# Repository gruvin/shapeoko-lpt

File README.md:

# Shapeoko UCCNC Upgrade

### Replacing [Shapeoko Pro XL](https://shop.carbide3d.com/collections/machines/products/shapeoko-pro-cnc-router?variant=33007028797501) basic stepper drivers and ditching GRBL in favour of advanced [UCCNC](https://cncdrive.com/UCCNC.html) Controller, using [UC100](https://cncdrive.com/UC100.html) USB interface to plug into this board.

## Why?

Mostly because I really like being able to pause, rewind, start, stop and see toolpaths in realtime. Call me old fashion. 

As a bonus, we get waaaaaay smoother, faster and generally more reliable stepper motors, using "proper" drivers.

## Features

Firstly, I didn't want to cut any wires ...

- Uses original Carbide3D Shapeoko power brick 24VDC @ 5A. (MOSFET switch and onboard 5V supply should handle double that V/A no problem.)
- Uses all original Shapeoko connectors for Power Switch (with blue LED), End Stops, BitSetter & BitZero. (An adapter board for the stepper motors is coming. The latter will be one each for the motor outputs on the stepper drivers.)

... etcetera ...
- Connects to your choice of "decent" stepper drivers

- Provides 24VDC/5A Charge Pump Switched power for drivers. Each of X/Y/Z ports has +5V/STEP/DIR/EN outputs (active low and Y1/Y2 are wired in parrallel or series. Your chpoice.)

- Built-in safety "charge pump" prevents 24VDC coming live until UCCNC is up and ready on the PC (can be bypassed with jumper.)

- VFD Spindle control with 0-10V speed control

- External 3 relay connector (4 if no charge pump). Relay 1 of 4 operates from EN (stepper enable). Relay 2 and 3 are connected to LPT P8 and P9 (Flood/Mist/Vacuum/Air.)

- Onboard 5VDC 1A supply.

- Input for **!! EMMERGENCY STOP !!** (normally closed switch.) Currently, the signal just goes to LPT P1, for your controller software (USCNC/Mach3) to deal with. Can use for that or Feed Hold if preferred.

## Status
### 2022-06-02 

First batch of assembled prototype PCBs were a bust due to both errors and having been obsoleted by lots of design changes since ordering them.

Trying to get a full week without making any chages before ordering a set of V2.0.

### KiCAD sneak peek, very much a work in progress ...

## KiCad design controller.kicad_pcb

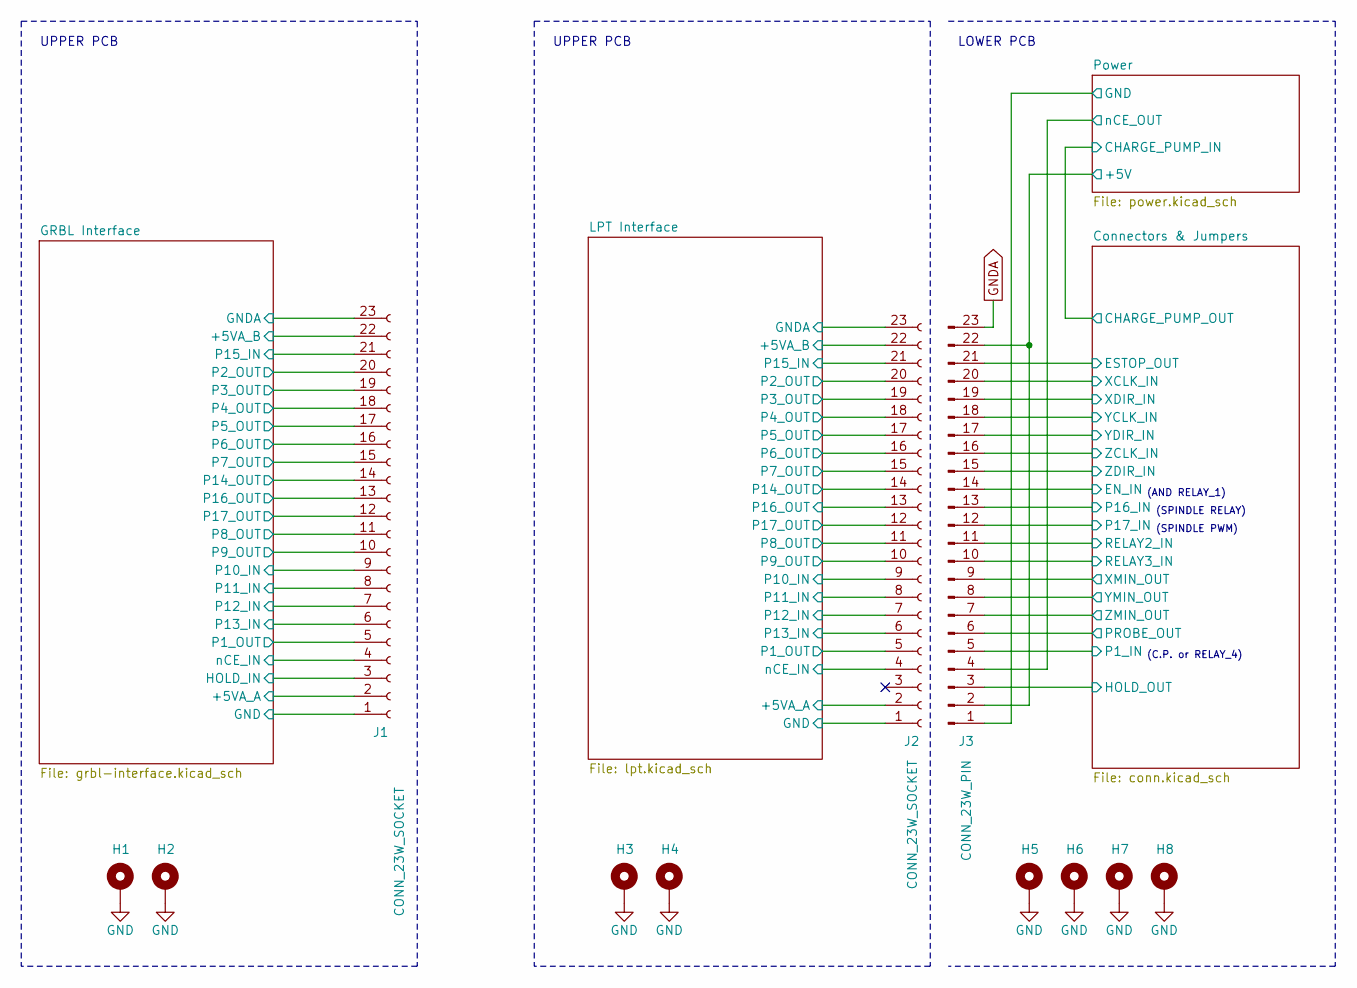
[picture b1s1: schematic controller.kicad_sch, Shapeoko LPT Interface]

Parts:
H1, H2, H3, H4, H6, H8: MountingHole_Pad; MountingHole_3.2mm_M3_ISO14580_Pad; JLCPART DNI
H5, H7: MountingHole_Pad; MountingHole_3.2mm_M3_ISO14580_Pad; JLCMFR# DNI
J1, J2: CONN_23W_SOCKET; PinSocket_1x23_P2.54mm_Vertical; LCSC C41376162
J3: CONN_23W_PIN; PinHeader_1x23_P2.54mm_Vertical

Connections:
+5V: J3.2, J3.22; also elsewhere on the board
+5VA: J1.2, J1.22, J2.2, J2.22; also elsewhere on the board
/Connectors & Jumpers/EN_IN: J3.14; also elsewhere on the board
/Connectors & Jumpers/ESTOP_OUT: J3.21; also elsewhere on the board
/Connectors & Jumpers/HOLD_OUT: J3.3; also elsewhere on the board
/Connectors & Jumpers/P1_IN: J3.5; also elsewhere on the board
/Connectors & Jumpers/P16_IN: J3.13; also elsewhere on the board
/Connectors & Jumpers/P17_IN: J3.12; also elsewhere on the board
/Connectors & Jumpers/PROBE_OUT: J3.6; also elsewhere on the board
/Connectors & Jumpers/RELAY2_IN: J3.11; also elsewhere on the board
/Connectors & Jumpers/RELAY3_IN: J3.10; also elsewhere on the board
/Connectors & Jumpers/XCLK_IN: J3.20; also elsewhere on the board
/Connectors & Jumpers/XDIR_IN: J3.19; also elsewhere on the board
/Connectors & Jumpers/XMIN_OUT: J3.9; also elsewhere on the board
/Connectors & Jumpers/YCLK_IN: J3.18; also elsewhere on the board
/Connectors & Jumpers/YDIR_IN: J3.17; also elsewhere on the board
/Connectors & Jumpers/YMIN_OUT: J3.8; also elsewhere on the board
/Connectors & Jumpers/ZCLK_IN: J3.16; also elsewhere on the board
/Connectors & Jumpers/ZDIR_IN: J3.15; also elsewhere on the board
/Connectors & Jumpers/ZMIN_OUT: J3.7; also elsewhere on the board
/GRBL Interface/GNDA: J1.23
/GRBL Interface/HOLD_IN: J1.3; also elsewhere on the board
/GRBL Interface/MISO: J1.7; also elsewhere on the board
/GRBL Interface/MOSI: J1.12; also elsewhere on the board
/GRBL Interface/P1_OUT: J1.5
/GRBL Interface/P2_OUT: J1.20; also elsewhere on the board
/GRBL Interface/P3_OUT: J1.19; also elsewhere on the board
/GRBL Interface/P4_OUT: J1.18; also elsewhere on the board
/GRBL Interface/P5_OUT: J1.17; also elsewhere on the board
/GRBL Interface/P6_OUT: J1.16; also elsewhere on the board
/GRBL Interface/P7_OUT: J1.15; also elsewhere on the board
/GRBL Interface/P8_OUT: J1.11; also elsewhere on the board
/GRBL Interface/P9_OUT: J1.10; also elsewhere on the board
/GRBL Interface/P10_IN: J1.9; also elsewhere on the board
/GRBL Interface/P11_IN: J1.8; also elsewhere on the board
/GRBL Interface/P13_IN: J1.6; also elsewhere on the board
/GRBL Interface/P14_OUT: J1.14; also elsewhere on the board
/GRBL Interface/P15_IN: J1.21; also elsewhere on the board
/GRBL Interface/SCK: J1.13; also elsewhere on the board
/GRBL Interface/nCE_IN: J1.4
/LPT Interface/P1_OUT: J2.5; also elsewhere on the board
/LPT Interface/P2_OUT: J2.20; also elsewhere on the board
/LPT Interface/P3_OUT: J2.19; also elsewhere on the board
/LPT Interface/P4_OUT: J2.18; also elsewhere on the board
/LPT Interface/P5_OUT: J2.17; also elsewhere on the board
/LPT Interface/P6_OUT: J2.16; also elsewhere on the board
/LPT Interface/P7_OUT: J2.15; also elsewhere on the board
/LPT Interface/P8_OUT: J2.11; also elsewhere on the board
/LPT Interface/P9_OUT: J2.10; also elsewhere on the board
/LPT Interface/P10_IN: J2.9; also elsewhere on the board
/LPT Interface/P11_IN: J2.8; also elsewhere on the board
/LPT Interface/P12_IN: J2.7; also elsewhere on the board
/LPT Interface/P13_IN: J2.6; also elsewhere on the board
/LPT Interface/P14_OUT: J2.14; also elsewhere on the board
/LPT Interface/P15_IN: J2.21; also elsewhere on the board
/LPT Interface/P16_OUT: J2.13; also elsewhere on the board
/LPT Interface/P17_OUT: J2.12; also elsewhere on the board
/LPT Interface/nCE_IN: J2.4; also elsewhere on the board
/Power/nCE_OUT: J3.4; also elsewhere on the board
GND: H1.1 (1_1), H2.1 (1_1), H3.1 (1_1), H4.1 (1_1), H5.1 (1_1), H6.1 (1_1), H7.1 (1_1), H8.1 (1_1), J2.1, J3.1; also elsewhere on the board
GND2: J1.1; also elsewhere on the board
GNDA: J2.23, J3.23; also elsewhere on the board

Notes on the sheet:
UPPER PCB
LOWER PCB
(C.P. or RELAY_4)
(SPINDLE PWM)
(SPINDLE RELAY)
(AND RELAY_1)

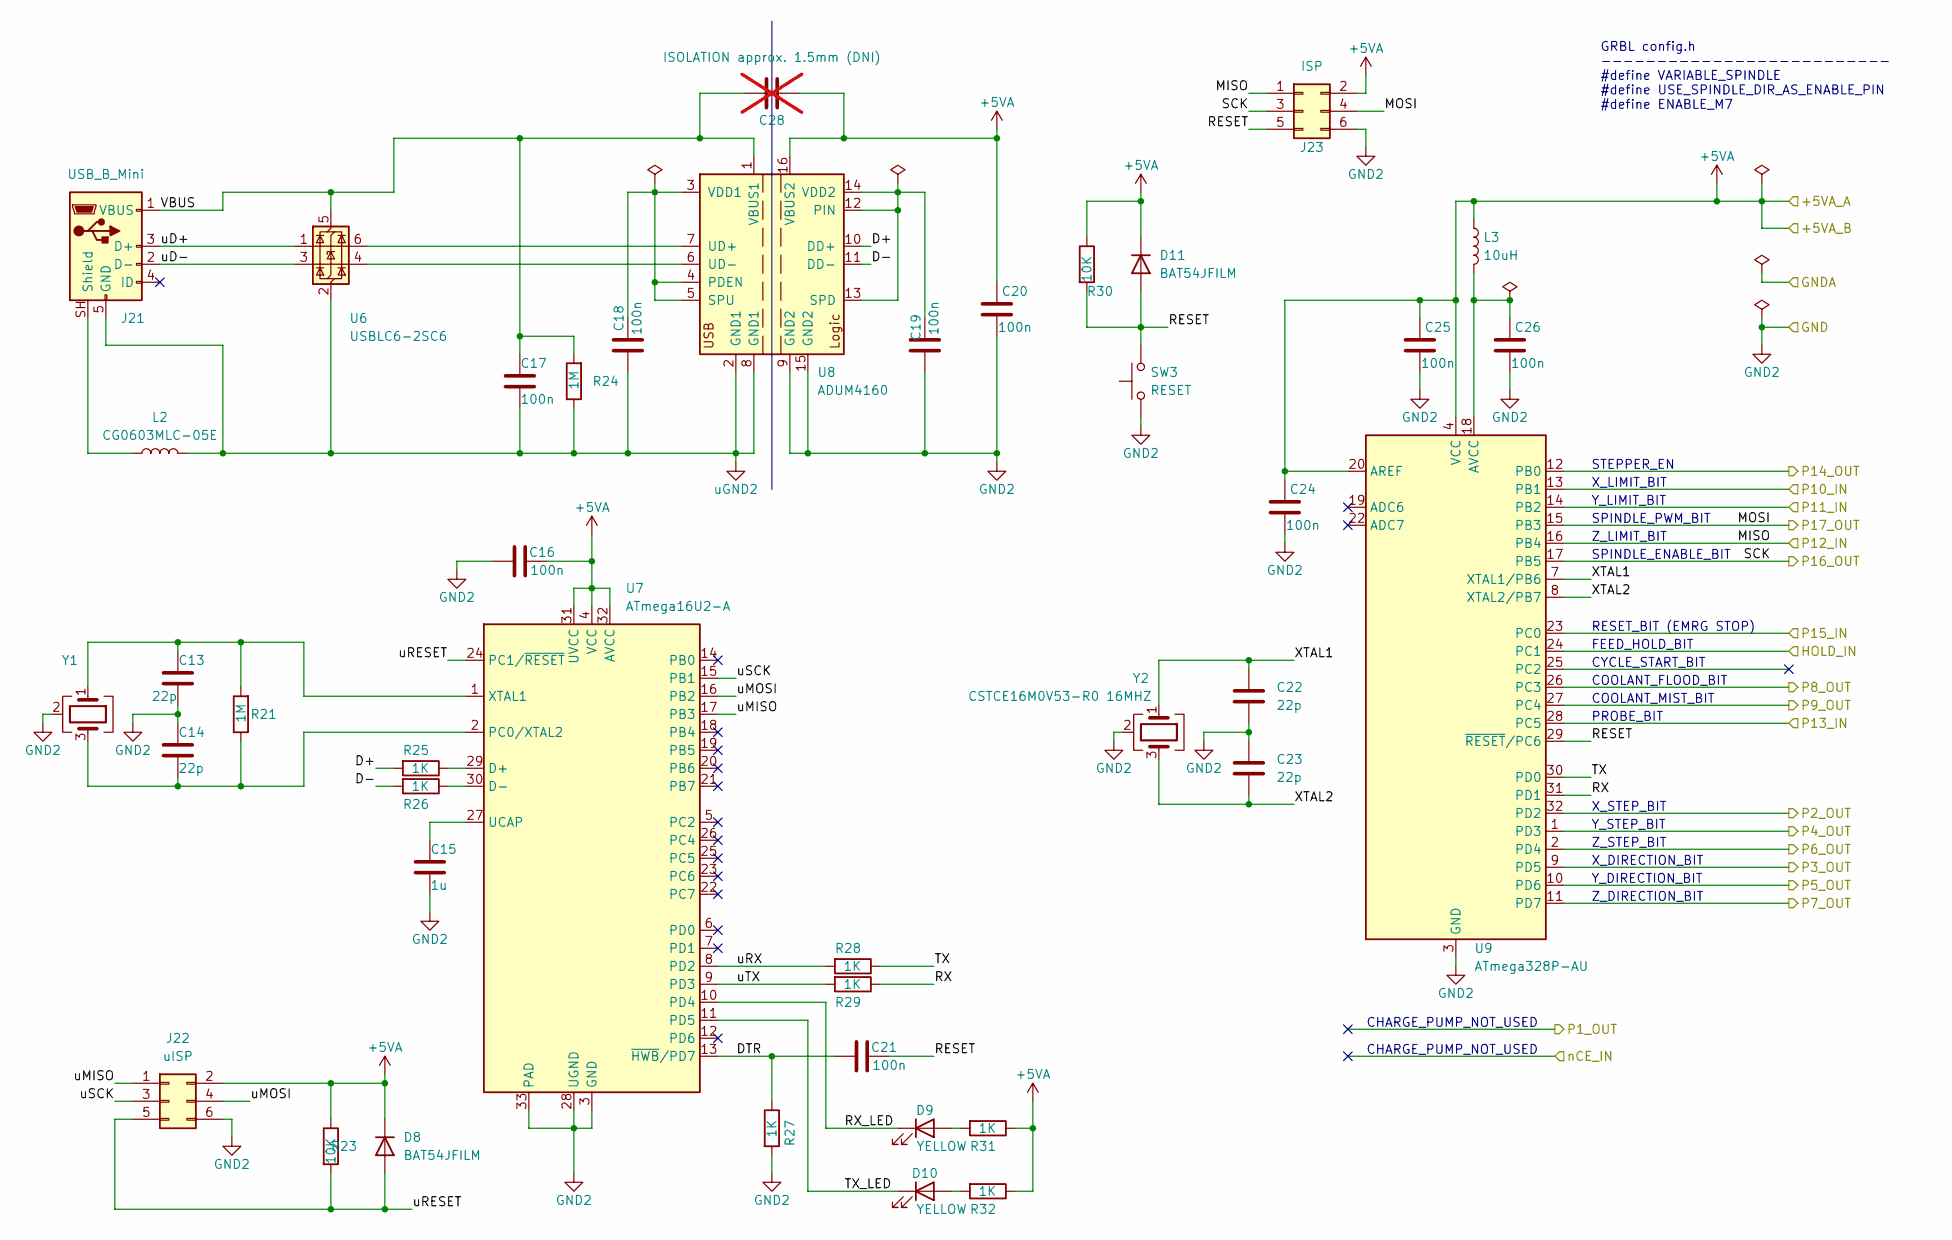
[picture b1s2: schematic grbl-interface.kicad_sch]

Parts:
C13, C14, C22, C23: 22p; C_0402_1005Metric_Pad0.74x0.62mm_HandSolder
C15: 1u; C_0603_1608Metric
C16, C24, C25, C26: 100n; C_0603_1608Metric
C17, C18, C19, C20, C21: 100n; C_0402_1005Metric_Pad0.74x0.62mm_HandSolder
C28: ISOLATION approx. 1.5mm (DNI); not fitted
D8, D11: BAT54JFILM; D_SOD-523_DOT
D9, D10: YELLOW; LED_0402_DOT
J21: USB_B_Mini; USB_Mini-B_Wuerth_65100516121_Horizontal
J22: uISP; ISP_SMD_100mil
J23: ISP; ISP_SMD_100mil
L2: CG0603MLC-05E; R_0805_2012Metric_Pad1.20x1.40mm_HandSolder
L3: 10uH; L_0603_1608Metric
R21, R24: 1M; R_0402_1005Metric_Pad0.72x0.64mm_HandSolder
R23, R30: 10K; R_0402_1005Metric_Pad0.72x0.64mm_HandSolder
R25, R26, R27, R28, R29, R31, R32: 1K; R_0402_1005Metric_Pad0.72x0.64mm_HandSolder
SW3: RESET; SW_Push_1P1T_NO_XUNPU_TS-1088-AR02016; LCSC C720477
U6: USBLC6-2SC6; SOT-23-6
U7: ATmega16U2-A; VQFN-32-1EP_4x4mm_P0.4mm_EP2.8x2.8mm
U8: ADUM4160; SOIC-16W_7.5x10.3mm_P1.27mm
U9: ATmega328P-AU; TQFP-32_7x7mm_P0.8mm
Y1: Crystal_SMD_WE_CFPX-104-4Pin_5.0x3.2mm
Y2: CSTCE16M0V53-R0 16MHZ; Crystal_SMD_WE_CFPX-104-4Pin_5.0x3.2mm

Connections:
+5VA: C16.2, C20.2, C24.2, C25.2, C28.1, D8.1 (K), D11.1 (K), J22.2, J23.2, L3.1, R23.1, R30.1, R31.1, R32.1, U7.4 (VCC), U7.31 (UVCC), U7.32 (AVCC), U8.16 (VBUS2), U9.4 (VCC), U9.6 (VCC), U9.20 (AREF); also elsewhere on the board
/GRBL Interface/D+: R25.2, U8.10 (DD+)
/GRBL Interface/D-: R26.2, U8.11 (DD-)
/GRBL Interface/DTR: C21.1, R27.1, U7.13 (~HWB/PD7)
/GRBL Interface/HOLD_IN: U9.24 (PC1); also elsewhere on the board
/GRBL Interface/MISO: J23.1, U9.16 (PB4); also elsewhere on the board
/GRBL Interface/MOSI: J23.4, U9.15 (PB3); also elsewhere on the board
/GRBL Interface/P2_OUT: U9.32 (PD2); also elsewhere on the board
/GRBL Interface/P3_OUT: U9.9 (PD5); also elsewhere on the board
/GRBL Interface/P4_OUT: U9.1 (PD3); also elsewhere on the board
/GRBL Interface/P5_OUT: U9.10 (PD6); also elsewhere on the board
/GRBL Interface/P6_OUT: U9.2 (PD4); also elsewhere on the board
/GRBL Interface/P7_OUT: U9.11 (PD7); also elsewhere on the board
/GRBL Interface/P8_OUT: U9.26 (PC3); also elsewhere on the board
/GRBL Interface/P9_OUT: U9.27 (PC4); also elsewhere on the board
/GRBL Interface/P10_IN: U9.13 (PB1); also elsewhere on the board
/GRBL Interface/P11_IN: U9.14 (PB2); also elsewhere on the board
/GRBL Interface/P13_IN: U9.28 (PC5); also elsewhere on the board
/GRBL Interface/P14_OUT: U9.12 (PB0); also elsewhere on the board
/GRBL Interface/P15_IN: U9.23 (PC0); also elsewhere on the board
/GRBL Interface/RESET: C21.2, D11.2 (A), J23.5, R30.2, SW3.2, U9.29 (~RESET/PC6)
/GRBL Interface/RX: R29.1, U9.31 (PD1)
/GRBL Interface/RX_LED: D9.1 (K), U7.10 (PD4)
/GRBL Interface/SCK: J23.3, U9.17 (PB5); also elsewhere on the board
/GRBL Interface/TX: R28.1, U9.30 (PD0)
/GRBL Interface/TX_LED: D10.1 (K), U7.11 (PD5)
/GRBL Interface/VBUS: C17.1, C28.2, J21.1 (VBUS), R24.2, U6.5 (VBUS), U8.1 (VBUS1)
/GRBL Interface/XTAL1: C22.1, U9.7 (XTAL1/PB6), Y2.1
/GRBL Interface/XTAL2: C23.2, U9.8 (XTAL2/PB7), Y2.3
/GRBL Interface/uD+: J21.3 (D+), U6.1 (I/O1)
/GRBL Interface/uD-: J21.2 (D-), U6.3 (I/O2)
/GRBL Interface/uMISO: J22.1, U7.17 (PB3)
/GRBL Interface/uMOSI: J22.4, U7.16 (PB2)
/GRBL Interface/uRESET: D8.2 (A), J22.5, R23.2, U7.24 (PC1/~RESET)
/GRBL Interface/uRX: R28.2, U7.8 (PD2)
/GRBL Interface/uSCK: J22.3, U7.15 (PB1)
/GRBL Interface/uTX: R29.2, U7.9 (PD3)
GND2: C13.2, C14.1, C15.2, C16.1, C19.2, C20.1, C22.2, C23.1, C24.1, C25.1, C26.1, J22.6, J23.6, R27.2, SW3.1, U7.3 (GND), U7.28 (UGND), U7.33 (PAD), U8.9 (GND2), U8.15 (GND2), U9.3 (GND), U9.5 (GND), U9.21 (GND), Y1.2 (G), Y1.4 (G), Y2.2 (G), Y2.4 (G); also elsewhere on the board
unnamed: D9.2 (A), R31.2
unnamed: D10.2 (A), R32.2
unnamed: J21.SH (Shield), L2.1
unnamed: R25.1, U7.29 (D+)
unnamed: R26.1, U7.30 (D-)
unnamed: C14.2, R21.1, U7.2 (PC0/XTAL2), Y1.3
unnamed: C15.1, U7.27 (UCAP)
unnamed: C13.1, R21.2, U7.1 (XTAL1), Y1.1
unnamed: C18.2, U8.3 (VDD1), U8.4 (PDEN), U8.5 (SPU)
unnamed: C19.1, U8.12 (PIN), U8.13 (SPD), U8.14 (VDD2)
unnamed: U6.6 (I/O1), U8.7 (UD+)
unnamed: U6.4 (I/O2), U8.6 (UD-)
unnamed: C26.2, L3.2, U9.18 (AVCC)
uGND2: C17.2, C18.1, J21.5 (GND), L2.2, R24.1, U6.2 (GND), U8.2 (GND1), U8.8 (GND1)

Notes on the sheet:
Y_LIMIT_BIT
X_LIMIT_BIT
SPINDLE_ENABLE_BIT
X_STEP_BIT
SPINDLE_PWM_BIT
CHARGE_PUMP_NOT_USED
CYCLE_START_BIT
RESET_BIT (EMRG STOP)
STEPPER_EN
X_DIRECTION_BIT
Z_STEP_BIT
Y_STEP_BIT
FEED_HOLD_BIT
PROBE_BIT
Z_DIRECTION_BIT
Z_LIMIT_BIT
COOLANT_FLOOD_BIT
Y_DIRECTION_BIT
COOLANT_MIST_BIT
GRBL config.h -------------------------- #define VARIABLE_SPINDLE #define USE_SPINDLE_DIR_AS_ENABLE_PIN #define ENABLE_M7

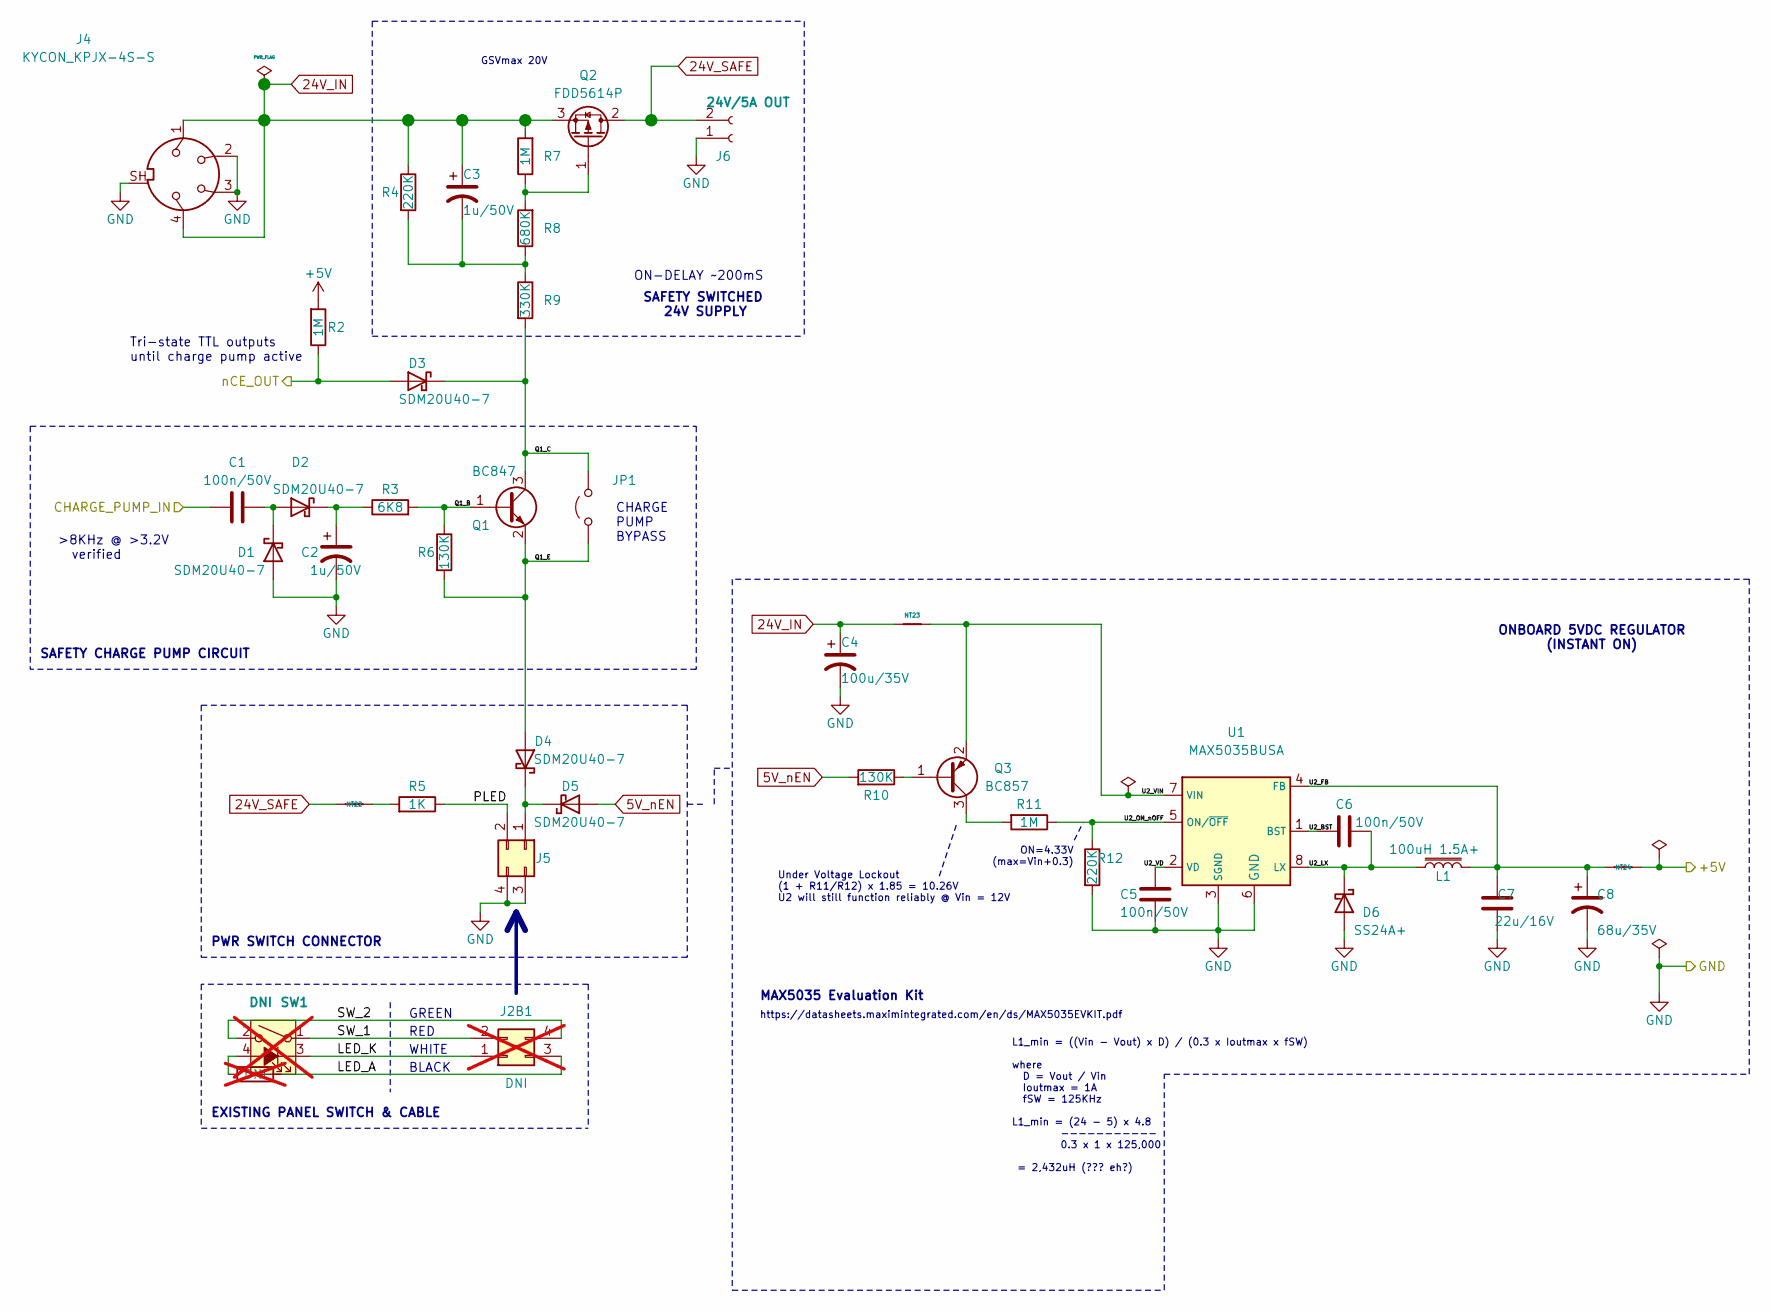
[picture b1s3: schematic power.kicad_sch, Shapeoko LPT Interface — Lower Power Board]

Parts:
C1: 100n/50V; C_0603_1608Metric; JLCMFR# 0603B103K500NT
C2, C3: 1u/50V; C_0603_1608Metric; JLCMFR# CL10A105KB8NNNC
C4: 100u/35V; CP_Elec_8x10.5_DOT; JLCPART C310848
C5, C6: 100n/50V; C_0603_1608Metric; JLCMFR# CC0603KRX7R9BB104
C7: 22u/16V; C_1206_3216Metric; JLCMFR# CC0603KRX7R9BB104
C8: 68u/35V; CP_Elec_6.3x7.7_DOT; JLCPART C178649
D1, D2, D3, D4, D5: SDM20U40-7; D_SOD-523; JLCPART C139439
D6: SS24A+; D_SMA_DOT; JLCPART C84503
J2B1: DNI; JLCPART DNI; not fitted
J4: KYCON_KPJX-4S-S; JLCPART Mouser
J5: MicroFit_2x02; Molex_Micro-Fit_3.0_43045-0412_2x02_P3.00mm_Vertical; JLCPART Mouser
J6: 24V/5A OUT; TerminalBlock_Phoenix_MKDS-1,5-2-5.08_1x02_P5.08mm_Horizont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; JLCPART C91153
JP1: Jumper_2_Bridged; PinHeader_2x01_P2.54mm_Vertical; JLCMFR# DNI
L1: 100uH 1.5A+; L_12x12mm_H6mm; JLCMFR# SRR1280A-101M
NT22: DNI; NetTie-2_SMD_Pad0.3mm; JLCMFR# DNI
NT23, NT24: DNI; NetTie-2_SMD_Pad1.0mm; JLCMFR# DNI
Q1: BC847; SOT-23; JLCMFR# BC847C,215
Q2: FDD5614P; TO-252-2
Q3: BC857; SOT-23; JLCMFR# BC857C,215
R1: DNI; R_0603_1608Metric; JLCMFR# DNI; not fitted
R2, R7, R11: 1M; R_0603_1608Metric; JLCMFR# 0603WAF1004T5E
R3: 6K8; R_0603_1608Metric; JLCMFR# 0603WAF6801T5E
R4, R12: 220K; R_0603_1608Metric; JLCMFR# 0603WAF2203T5E
R5: 1K; R_0603_1608Metric; JLCMFR# 0603WAF1001T5E
R6, R10: 130K; R_0603_1608Metric; JLCMFR# 0603WAF1303T5E
R8: 680K; R_0603_1608Metric; JLCMFR# 0603WAF6803T5E
R9: 330K; R_0603_1608Metric; JLCMFR# 0603WAF3303T5E
SW1: DNI; JLCMFR# DNI; not fitted
U1: MAX5035BUSA; SOIC-8_3.9x4.9mm_P1.27mm; JLCMFR# MAX5035BASA+T

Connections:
5V_nEN: D5.2 (A), R10.2
24V_IN: C3.1, C4.1, J4.1, J4.4, NT23.1, Q2.3 (S), R4.1, R7.2
24V_SAFE: J6.2, NT22.2, Q2.2 (D); also elsewhere on the board
+5V: NT24.2, R2.2; also elsewhere on the board
/Connectors & Jumpers/CHARGE_PUMP_OUT: C1.1; also elsewhere on the board
/Power/PLED: J5.2, R5.1
/Power/Q1_B: Q1.1 (B), R3.2, R6.1
/Power/Q1_C: D3.1 (K), JP1.2 (B), Q1.3 (C), R9.2
/Power/Q1_E: D4.2 (A), JP1.1 (A), Q1.2 (E), R6.2
/Power/U2_BST: C6.1, U1.1 (BST)
/Power/U2_FB: C7.2, C8.1, L1.2, NT24.1, U1.4 (FB)
/Power/U2_LX: C6.2, D6.1 (K), L1.1, U1.8 (LX)
/Power/U2_ON_nOFF: R11.1, R12.1, U1.5 (ON/~OFF)
/Power/U2_VD: C5.1, U1.2 (VD)
/Power/U2_VIN: NT23.2, Q3.2 (E), U1.7 (VIN)
/Power/nCE_OUT: D3.2 (A), R2.1; also elsewhere on the board
GND: C2.2, C4.2, C5.2, C7.1, C8.2, D1.2 (A), D6.2 (A), J4.2, J4.3, J4.SH, J5.3, J5.4, J6.1, R12.2, U1.3 (SGND), U1.6 (GND); also elsewhere on the board
unnamed: C3.2, R4.2, R8.1, R9.1
unnamed: C1.2, D1.1 (K), D2.2 (A)
unnamed: C2.1, D2.1 (K), R3.1
unnamed: D4.1 (K), D5.1 (K), J5.1
unnamed: J2B1.1, SW1.3 (K)
unnamed: J2B1.2, SW1.1
unnamed: J2B1.3, R1.1
unnamed: J2B1.4, SW1.2
unnamed: NT22.1, R5.2
unnamed: Q2.1 (G), R7.1, R8.2
unnamed: Q3.1 (B), R10.1
unnamed: Q3.3 (C), R11.2
unnamed: R1.2, SW1.4 (A)

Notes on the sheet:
Under Voltage Lockout (1 + R11/R12) x 1.85 = 10.26V U2 will still function reliably @ Vin = 12V
ON-DELAY ~200mS
GREEN
CHARGE PUMP BYPASS
MAX5035 Evaluation Kit
EXISTING PANEL SWITCH & CABLE
https://datasheets.maximintegrated.com/en/ds/MAX5035EVKIT.pdf
Tri-state TTL outputs until charge pump active
PWR SWITCH CONNECTOR
L1_min = ((Vin - Vout) x D) / (0.3 x Ioutmax x fSW) where D = Vout / Vin Ioutmax = 1A fSW = 125KHz L1_min = (24 - 5) x 4.8 ----------- 0.3 x 1 x 125,000 = 2,432uH (??? eh?)
ON=4.33V (max=Vin+0.3)
SAFETY SWITCHED 24V SUPPLY
WHITE
ONBOARD 5VDC REGULATOR (INSTANT ON)
>8KHz @ >3.2V verified
SAFETY CHARGE PUMP CIRCUIT
BLACK
RED
GSVmax 20V

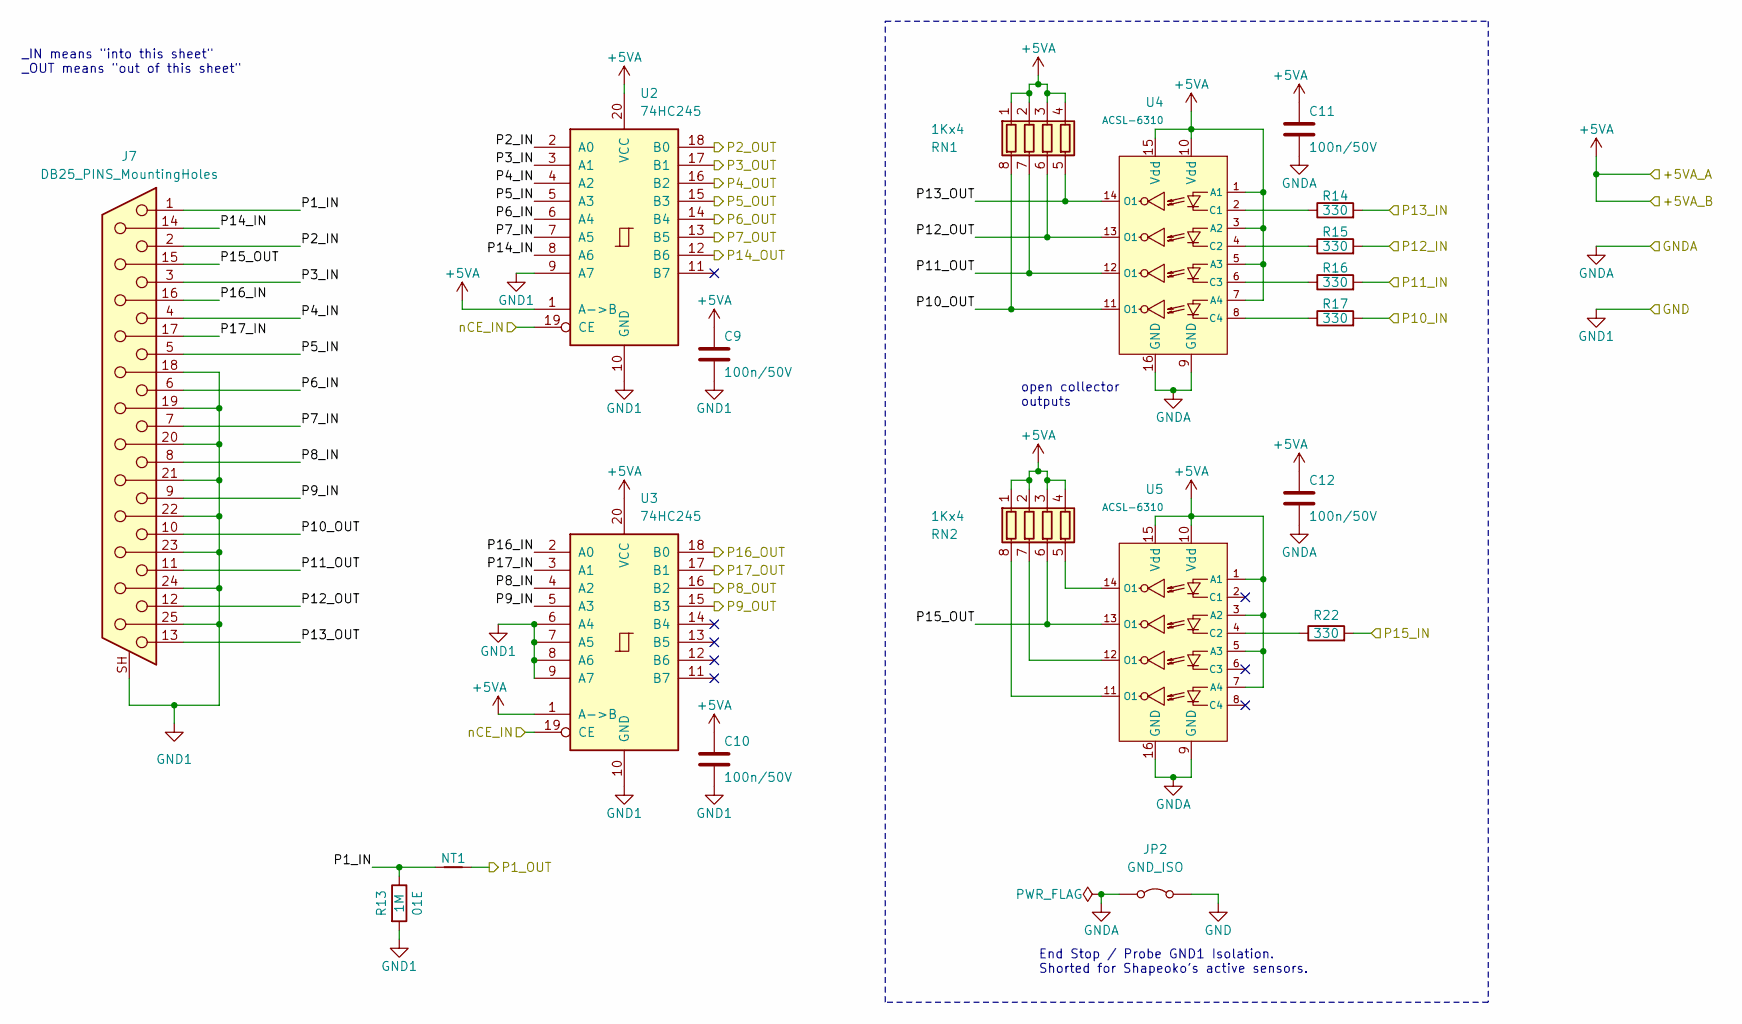
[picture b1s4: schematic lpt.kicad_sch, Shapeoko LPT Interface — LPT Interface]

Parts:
C9, C10, C11, C12: 100n/50V; C_0603_1608Metric; JLCMFR# CC0603KRX7R9BB104
J7: DB25_PINS_MountingHoles; DSUB-25_Pins_Horizontal_P2.77x2.84mm_EdgePinOffset7.70mm_Ho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
JP2: GND_ISO; PinHeader_1x02_P2.54mm_Vertical; JLCMFR# DNI
NT1: NetTie_2; NetTie-2_SMD_Pad0.3mm
R13: 1M; R_0603_1608Metric; JLCMFR# 0603WAF5601T5E
R14, R15, R16, R17: 330; R_0603_1608Metric; JLCMFR# 0603WAF5601T5E
R22: 330; R_0402_1005Metric_Pad0.72x0.64mm_HandSolder; JLCMFR# 0603WAF5601T5E
RN1, RN2: 1Kx4; R_Array_Convex_4x0603; JLCMFR# 4D03WGJ0102T5E
U2, U3: 74HC245; SOIC-20W_7.5x12.8mm_P1.27mm; JLCMFR# 74HC245D,653
U4, U5: ACSL-6310; SO-16_3.9x9.9mm_P1.27mm; JLCMFR# ACSL-6310-00TE

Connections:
+5VA: C9.1, C10.1, C11.1, C12.1, RN1.1 (R1.1), RN1.2 (R2.1), RN1.3 (R3.1), RN1.4 (R4.1), RN2.1 (R1.1), RN2.2 (R2.1), RN2.3 (R3.1), RN2.4 (R4.1), U2.1 (A->B), U2.20 (VCC), U3.1 (A->B), U3.20 (VCC), U4.1 (A1), U4.3 (A2), U4.5 (A3), U4.7 (A4), U4.10 (Vdd), U4.15 (Vdd), U5.1 (A1), U5.3 (A2), U5.5 (A3), U5.7 (A4), U5.10 (Vdd), U5.15 (Vdd); also elsewhere on the board
/LPT Interface/P1_IN: J7.1, NT1.1, R13.1
/LPT Interface/P1_OUT: NT1.2; also elsewhere on the board
/LPT Interface/P2_IN: J7.2, U2.2 (A0)
/LPT Interface/P2_OUT: U2.18 (B0); also elsewhere on the board
/LPT Interface/P3_IN: J7.3, U2.3 (A1)
/LPT Interface/P3_OUT: U2.17 (B1); also elsewhere on the board
/LPT Interface/P4_IN: J7.4, U2.4 (A2)
/LPT Interface/P4_OUT: U2.16 (B2); also elsewhere on the board
/LPT Interface/P5_IN: J7.5, U2.5 (A3)
/LPT Interface/P5_OUT: U2.15 (B3); also elsewhere on the board
/LPT Interface/P6_IN: J7.6, U2.6 (A4)
/LPT Interface/P6_OUT: U2.14 (B4); also elsewhere on the board
/LPT Interface/P7_IN: J7.7, U2.7 (A5)
/LPT Interface/P7_OUT: U2.13 (B5); also elsewhere on the board
/LPT Interface/P8_IN: J7.8, U3.4 (A2)
/LPT Interface/P8_OUT: U3.16 (B2); also elsewhere on the board
/LPT Interface/P9_IN: J7.9, U3.5 (A3)
/LPT Interface/P9_OUT: U3.15 (B3); also elsewhere on the board
/LPT Interface/P10_IN: R17.2; also elsewhere on the board
/LPT Interface/P10_OUT: J7.10, RN1.8 (R1.2), U4.11 (O1)
/LPT Interface/P11_IN: R16.2; also elsewhere on the board
/LPT Interface/P11_OUT: J7.11, RN1.7 (R2.2), U4.12 (O1)
/LPT Interface/P12_IN: R15.2; also elsewhere on the board
/LPT Interface/P12_OUT: J7.12, RN1.6 (R3.2), U4.13 (O1)
/LPT Interface/P13_IN: R14.2; also elsewhere on the board
/LPT Interface/P13_OUT: J7.13, RN1.5 (R4.2), U4.14 (O1)
/LPT Interface/P14_IN: J7.14, U2.8 (A6)
/LPT Interface/P14_OUT: U2.12 (B6); also elsewhere on the board
/LPT Interface/P15_IN: R22.2; also elsewhere on the board
/LPT Interface/P15_OUT: J7.15, RN2.6 (R3.2), U5.13 (O1)
/LPT Interface/P16_IN: J7.16, U3.2 (A0)
/LPT Interface/P16_OUT: U3.18 (B0); also elsewhere on the board
/LPT Interface/P17_IN: J7.17, U3.3 (A1)
/LPT Interface/P17_OUT: U3.17 (B1); also elsewhere on the board
/LPT Interface/nCE_IN: U2.19 (CE), U3.19 (CE); also elsewhere on the board
GND: C9.2, C10.2, J7.18, J7.19, J7.20, J7.21, J7.22, J7.23, J7.24, J7.25, J7.SH (PAD), JP2.2 (B), R13.2, U2.9 (A7), U2.10 (GND), U3.6 (A4), U3.7 (A5), U3.8 (A6), U3.9 (A7), U3.10 (GND); also elsewhere on the board
GNDA: C11.2, C12.2, JP2.1 (A), U4.9 (GND), U4.16 (GND), U5.9 (GND), U5.16 (GND); also elsewhere on the board
unnamed: RN2.8 (R1.2), U5.11 (O1)
unnamed: RN2.7 (R2.2), U5.12 (O1)
unnamed: RN2.5 (R4.2), U5.14 (O1)
unnamed: R14.1, U4.2 (C1)
unnamed: R15.1, U4.4 (C2)
unnamed: R16.1, U4.6 (C3)
unnamed: R17.1, U4.8 (C4)
unnamed: R22.1, U5.4 (C2)

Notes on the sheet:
End Stop / Probe GND1 Isolation. Shorted for Shapeoko's active sensors.
_IN means "into this sheet" _OUT means "out of this sheet"
open collector outputs

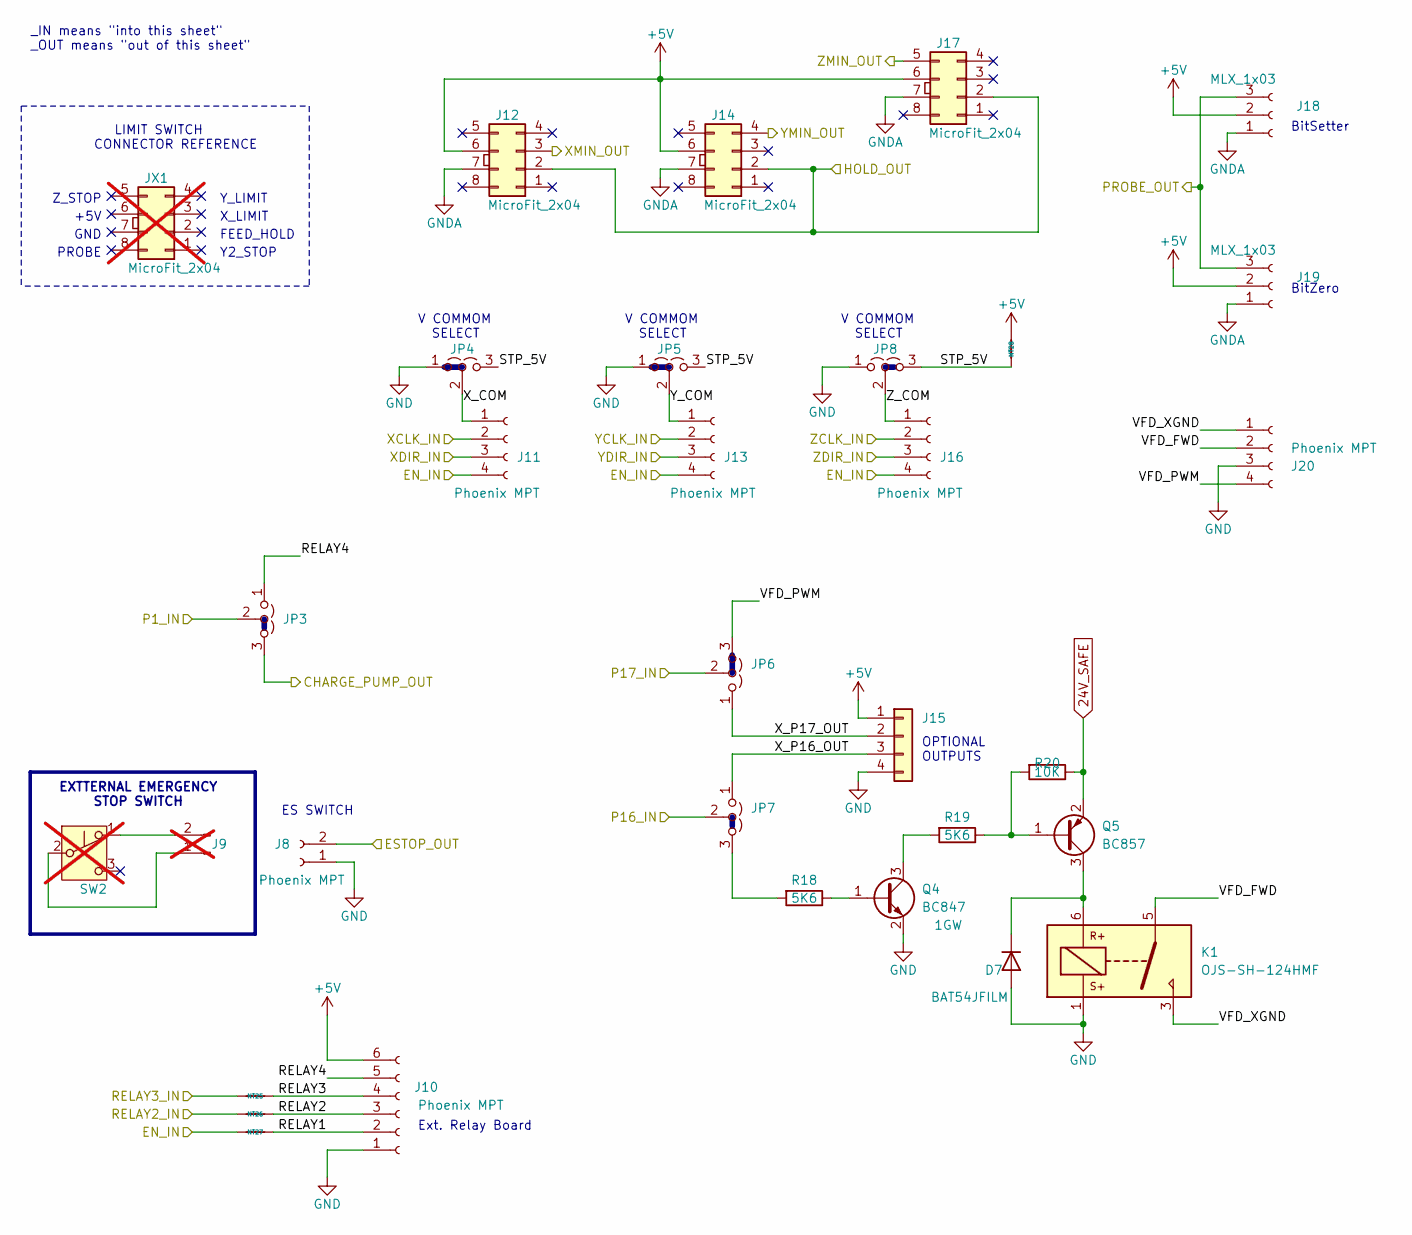
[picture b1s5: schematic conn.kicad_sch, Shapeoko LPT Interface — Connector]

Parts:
D7: BAT54JFILM; D_SOD-523_DOT; JLCMFR# BAT54JFILM
J8: Phoenix MPT; TerminalBlock_Phoenix_MPT-0,5-2-2.54_1x02_P2.54mm_Horizontal; JLCMFR# KF128-2.54-2P
J9: DNI; JLCMFR# DNI; not fitted
J10: Phoenix MPT; TerminalBlock_Phoenix_MPT-0,5-6-2.54_1x06_P2.54mm_Horizontal; JLCMFR# KF128-2.54-6P
J11, J13, J16, J20: Phoenix MPT; TerminalBlock_Phoenix_MPT-0,5-4-2.54_1x04_P2.54mm_Horizontal; JLCMFR# KF128-2.54-4P
J12, J14, J17: MicroFit_2x04; Molex_Micro-Fit_3.0_43045-0812_2x04_P3.00mm_Vertical; JLCMFR# 538-43045-1027
J15: JST_B2B-XH; TerminalBlock_Phoenix_MPT-0,5-4-2.54_1x04_P2.54mm_Horizontal; JLCMFR# B2B-XH-A(LF)(SN)
J18, J19: MLX_1x03; Molex_KK-254_AE-6410-03A_1x03_P2.54mm_Vertical; JLCMFR# 22232031
JP3, JP6, JP7: 1x03_2.54; PinHeader_1x03_P2.54mm_Vertical; JLCMFR# DNI
JP4, JP5, JP8: Jumper_3_Open; PinHeader_1x03_P2.54mm_Vertical; JLCMFR# DNI
JX1: MicroFit_2x04; Molex_Micro-Fit_3.0_43045-0812_2x04_P3.00mm_Vertical; JLCMFR# 538-43045-1027; not fitted
K1: OJS-SH-124HMF; Relay_SPST_OJS_24V_10A; DIGIPART 41-OJS-SH-124HMF,00000-ND
NT25, NT26, NT27: DNI; NetTie-2_SMD_Pad0.3mm; JLCMFR# DNI
NT28: DNI; NetTie-2_SMD_Pad1.0mm; JLCMFR# DNI
Q4: BC847; SOT-23; JLCMFR# BC847C,215
Q5: BC857; SOT-23_DOT; JLCMFR# BC857C,215
R18, R19: 5K6; R_0603_1608Metric; JLCMFR# 0603WAF5601T5E
R20: 10K; R_0603_1608Metric; JLCMFR# 0603WAF1002T5E
SW2: DNI; JLCMFR# DNI; not fitted

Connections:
24V_SAFE: Q5.2 (E), R20.1; also elsewhere on the board
+5V: J10.6, J12.6, J14.6, J15.1, J17.6, J18.2, J19.2, NT28.2; also elsewhere on the board
/Connectors & Jumpers/CHARGE_PUMP_OUT: JP3.3 (B); also elsewhere on the board
/Connectors & Jumpers/EN_IN: J11.4, J13.4, J16.4, NT27.1; also elsewhere on the board
/Connectors & Jumpers/ESTOP_OUT: J8.2; also elsewhere on the board
/Connectors & Jumpers/HOLD_OUT: J12.2, J14.2, J17.2; also elsewhere on the board
/Connectors & Jumpers/P1_IN: JP3.2 (C); also elsewhere on the board
/Connectors & Jumpers/P16_IN: JP7.2 (C); also elsewhere on the board
/Connectors & Jumpers/P17_IN: JP6.2 (C); also elsewhere on the board
/Connectors & Jumpers/PROBE_OUT: J18.3, J19.3; also elsewhere on the board
/Connectors & Jumpers/RELAY1: J10.2, NT27.2
/Connectors & Jumpers/RELAY2: J10.3, NT26.2
/Connectors & Jumpers/RELAY2_IN: NT26.1; also elsewhere on the board
/Connectors & Jumpers/RELAY3: J10.4, NT25.2
/Connectors & Jumpers/RELAY3_IN: NT25.1; also elsewhere on the board
/Connectors & Jumpers/RELAY4: J10.5, JP3.1 (A)
/Connectors & Jumpers/STP_5V: JP4.3 (B), JP5.3 (B), JP8.3 (B), NT28.1
/Connectors & Jumpers/VFD_FWD: J20.2, K1.5
/Connectors & Jumpers/VFD_PWM: J20.4, JP6.3 (B)
/Connectors & Jumpers/VFD_XGND: J20.1, K1.3
/Connectors & Jumpers/XCLK_IN: J11.2; also elsewhere on the board
/Connectors & Jumpers/XDIR_IN: J11.3; also elsewhere on the board
/Connectors & Jumpers/XMIN_OUT: J12.3; also elsewhere on the board
/Connectors & Jumpers/X_COM: J11.1, JP4.2 (C)
/Connectors & Jumpers/X_P16_OUT: J15.3, JP7.1 (A)
/Connectors & Jumpers/X_P17_OUT: J15.2, JP6.1 (A)
/Connectors & Jumpers/YCLK_IN: J13.2; also elsewhere on the board
/Connectors & Jumpers/YDIR_IN: J13.3; also elsewhere on the board
/Connectors & Jumpers/YMIN_OUT: J14.4; also elsewhere on the board
/Connectors & Jumpers/Y_COM: J13.1, JP5.2 (C)
/Connectors & Jumpers/ZCLK_IN: J16.2; also elsewhere on the board
/Connectors & Jumpers/ZDIR_IN: J16.3; also elsewhere on the board
/Connectors & Jumpers/ZMIN_OUT: J17.5; also elsewhere on the board
/Connectors & Jumpers/Z_COM: J16.1, JP8.2 (C)
GND: D7.2 (A), J8.1, J10.1, J15.4, J20.3, JP4.1 (A), JP5.1 (A), JP8.1 (A), K1.1, Q4.2 (E); also elsewhere on the board
GNDA: J12.7, J14.7, J17.7, J18.1, J19.1; also elsewhere on the board
unnamed: D7.1 (K), K1.6, Q5.3 (C)
unnamed: J9.1, SW2.2 (B)
unnamed: J9.2, SW2.1 (A)
unnamed: JP7.3 (B), R18.2
unnamed: Q4.1 (B), R18.1
unnamed: Q4.3 (C), R19.2
unnamed: Q5.1 (B), R19.1, R20.2

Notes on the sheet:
BitZero
OPTIONAL OUTPUTS
Y2_STOP
Y_LIMIT
+5V
BitSetter
Ext. Relay Board
PROBE
FEED_HOLD
V COMMOM SELECT
EXTTERNAL EMERGENCY STOP SWITCH
_IN means "into this sheet" _OUT means "out of this sheet"
GND
X_LIMIT
Z_STOP
ES SWITCH
LIMIT SWITCH CONNECTOR REFERENCE
